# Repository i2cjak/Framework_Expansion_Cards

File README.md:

# i2cjak on X.com is THE foremost hardware engineer and poaster. he is designing one (1) new Framework Expansion Card per day until they give him a REALLY NICE laptop

# PROOF OF CHALLENGE!

## [Day 1](./Day_01_Wi-Fi-HaLow/)

Wi-Fi HaLow

## [Day 2](./Day_02_Four_Port_USB_C/)

Four Port USB-C

## [Day 3](./Day_03_ECG_SPO2/)

Electrocardiogram + SPO2

## [Day 4](./Day_04_Frameoscope/)

Frameoscope

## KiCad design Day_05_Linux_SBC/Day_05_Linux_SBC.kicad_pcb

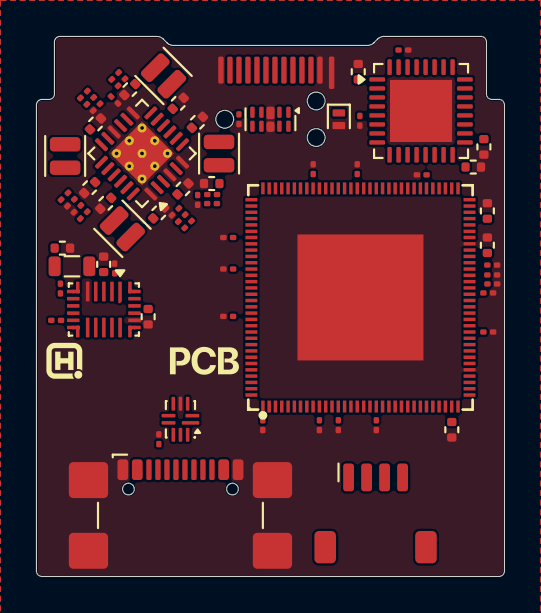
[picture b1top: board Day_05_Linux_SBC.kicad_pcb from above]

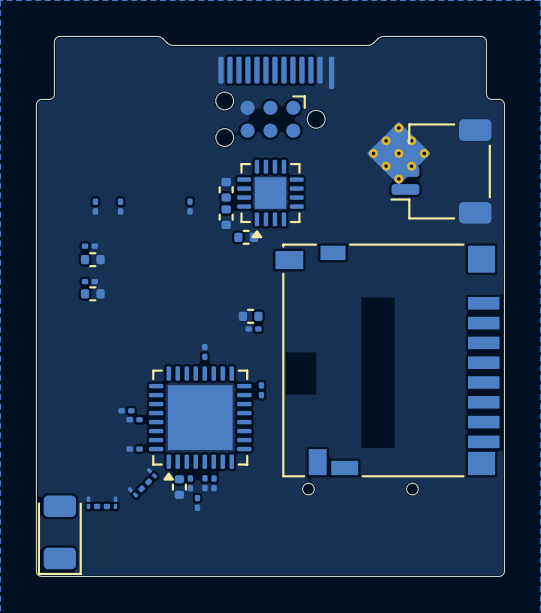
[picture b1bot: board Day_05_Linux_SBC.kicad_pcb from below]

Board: 8 copper layers, 26.0 x 30.0 mm, 108 parts (34 on the bottom side), 52 nets, no tracks yet.

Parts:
AE1: Antenna_Chip; Johanson_2450AT18x100_2400-2500Mhz
C1, C2, C4, C15, C16, C17, C18, C19, C23, C26, C38, C44, C45, C49, C55, C57, C64, C65, C66: 10uF; amemb-C_0402_1005Metric_L
C3, C21, C25, C27, C28, C29, C30, C31, C32, C33, C39, C40, C41, C42, C43, C46, C47, C48, C50, C51, C52, C53, C54, C56, C58, C59, C60, C61, C62, C63: 1uF; amemb-C_0201_0603Metric_L
C5, C6, C7, C10: 220pF; amemb-C_0201_0603Metric_L
C8: 47nF; amemb-C_0201_0603Metric_L
C9: 100nF; amemb-C_0201_0603Metric_L
C11, C12, C13, C14, C22: 22uF; amemb-C_0402_1005Metric_L
C20: 22nF; amemb-C_0201_0603Metric_L
C24: 4.7uF; amemb-C_0402_1005Metric_L
C34, C35, C36, C37: 1.2pF; amemb-C_01005_0402Metric_L
D1: TVS; D_SOD-882
H1, H2: MountingHole; MountingHole_2.2mm_M2
J1: USB_C_Plug_USB2.0; USB_C_Plug_Amphenol_12401981E412A
J2: Conn_ARM_SWD_TagConnect_TC2030-NL; Tag-Connect_TC2030-IDC-NL_2x03_P1.27mm_Vertical
J3: USB_C_Receptacle_USB2.0_14P; USB_C_Receptacle_GCT_USB4110
J4: JST SH SM03B; JST_SH_SM03B-SRSS-TB_1x03-1MP_P1.00mm_Horizontal
J5: Micro_SD_Card_Det2; microSD_HC_Hirose_DM3D-SF
L1, L2, L3, L4: 1.5uH; amemb-L_0806_2016Metric_L
L5: 1uH; amemb-L_0805_2012Metric_L
L6: 2.4nH; amemb-L_0201_0603Metric_L
L7: 0R; amemb-R_0201_0603Metric_L
LOGO1: NextPCB
R1: 5.1kR; amemb-R_0201_0603Metric_L
R2: 10kR; amemb-R_0201_0603Metric_L
R3, R13: 510kR; amemb-R_0201_0603Metric_L
R4, R5, R7, R9, R10, R12, R15, R16: 100kR; amemb-R_0201_0603Metric_L
R6: 80.6kR; amemb-R_0201_0603Metric_L
R8, R11: 200kR; amemb-R_0201_0603Metric_L
R14: 240R; amemb-R_0201_0603Metric_L
U1: D3V3XA4B10LP; Diodes_UDFN-10_1x2.5mm_P0.5mm
U2: STM32H503KBUx; QFN-32-1EP_5x5mm_P0.5mm_EP3.45x3.45mm
U3: CH334P; QFN-16-1EP_3x3mm_P0.5mm_EP1.75x1.75mm
U5: ESP32-C6FH4; QFN-32-1EP_5x5mm_P0.5mm_EP3.6x3.6mm
U6: RV1106G2; QFN-128_L12.3-W12.3-P0.35-TL-EP7.0-1
U7: STEMMA-QT; JST_SH_SM04B-SRSS-TB_1x04-1MP_P1.00mm_Horizontal
U8: EA3058QD; VQFN-24-1EP_4x4mm_P0.5mm_EP2.5x2.5mm_ThermalVias
U9: MP2722; QFN-22_MP2722_2.5x3.5mm_P0.4mm
U10: TS3USB30ERSWR; UQFN-10_1.4x1.8mm_P0.4mm

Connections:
+0V9: C7.1, C14.1, C38.1, C39.1, C40.1, C41.1, C46.1, C47.1, C48.1, C49.1, C50.1, C51.1, C52.1, L3.2, R7.1, U6.10 (VDD0V9), U6.51 (VDD0V9), U6.54 (VDD0V9), U6.55 (VDD0V9), U6.67 (VDD0V9), U6.71 (VDD0V9), U6.82 (VDD0V9), U6.103 (VDD0V9), U6.115 (VDD0V9), U6.116 (VDD0V9)
+1V8: C10.1, C12.1, C53.1, C54.1, C55.1, C58.1, L4.2, R11.1, U6.1 (GPIO7_VCC1V8), U6.24 (VDD1V8), U6.31 (VDD1V8), U6.53 (VDD1V8), U6.70 (VDD1V8), U6.96 (VDD1V8)
+1V35: C6.1, C13.1, C42.1, C43.1, C44.1, C45.1, L2.2, R5.1, U6.49 (DDR_VDDQ), U6.50 (DDR_VDDQ), U6.56 (DDR_VDDQ)
+3V3: C1.1, C2.1, C3.1, C5.1, C11.1, C25.1, C26.1, C27.1, C28.1, C29.1, C30.1, C31.1, C32.1, C33.1, C56.1, C57.1, C59.1, C60.1, C61.1, C62.1, C63.1, J2.1 (VCC), L1.2, R3.1, R16.1, U2.1 (VDD), U2.5 (VDDA), U2.17 (VDD), U5.2 (VDDA3P3), U5.3 (VDDA3P3), U5.5 (VDDPST1), U5.20 (VDDPST2), U5.29 (VDDA1), U5.32 (VDDA2), U6.13 (GPIO4_VCC), U6.19 (VDD3V3), U6.28 (VDD3V3), U6.43 (GPIO3_VCC), U6.61 (VDD3V3), U6.81 (VDD3V3), U6.88 (GPIO6_VCC), U6.101 (VDD3V3), U6.108 (GPIO5_VCC), U10.8 (~OE), U10.9 (VCC)
/D+: J1.A6 (D+), U1.4, U1.7 (NC), U3.12 (DPU+)
/D-: J1.A7 (D-), U1.2, U1.9 (NC), U3.11 (DMU-)
/ESP32-C6/ESP32.EN: R15.1, U5.4 (CHIP_PU)
/MPU_OUT.D+: J3.A6 (D+), J3.B6 (D+), U10.1 (D1+)
/MPU_OUT.D-: J3.A7 (D-), J3.B7 (D-), U10.7 (D1-)
/PMIC.CC1: J3.A5 (CC1), U9.1 (CC1)
/PMIC.CC2: J3.B5 (CC2), U9.22 (CC2)
/Power Supply/NTC: J4.2, R13.1, U9.10 (NTC1)
/Power Supply/VBUS_IO: C21.1, U9.2 (IN)
/RV1106G2/MPU.D+: U6.27 (USB_DP), U10.3 (D+)
/RV1106G2/MPU.D-: U6.26 (USB_DM), U10.5 (D-)
/STM32H5/SWCLK: J2.4 (SWCLK), U2.24 (DEBUG_JTCK-SWCLK)
/STM32H5/SWDIO: J2.2 (SWDIO), U2.23 (DEBUG_JTMS-SWDIO)
/STM32H5/~RESET: J2.3 (~RESET), U2.4 (NRST)
GND: C1.2, C2.2, C3.2, C4.2, C8.2, C9.2, C11.2, C12.2, C13.2, C14.2, C15.2, C16.2, C17.2, C18.2, C19.2, C21.2, C22.2, C23.2, C24.2, C25.2, C26.2, C27.2, C28.2, C29.2, C30.2, C31.2, C32.2, C33.2, C34.2, C35.2, C36.2, C37.2, C38.2, C39.2, C40.2, C41.2, C42.2, C43.2, C44.2, C45.2, C46.2, C47.2, C48.2, C49.2, C50.2, C51.2, C52.2, C53.2, C54.2, C55.2, C56.2, C57.2, C58.2, C59.2, C60.2, C61.2, C62.2, C63.2, C64.2, C65.2, C66.2, D1.2 (A), J1.A1 (GND), J1.A12 (GND), J1.B1 (GND), J1.B12 (GND), J1.SH (SHIELD), J2.5 (GND), J3.A1 (GND), J3.A12 (GND), J3.B1 (GND), J3.B12 (GND), J3.SH (SHIELD), J4.3, J4.MP (MountPin), R1.2, R2.2, R4.2, R6.2, R8.2, R12.2, R14.2, R15.2, U1.3 (VSS), U1.8 (VSS), U2.33 (VSS), U3.17 (GND), U5.33 (GND), U6.37 (VSS), U6.57 (VSS), U6.129 (VSS), U8.1 (GND), U8.4 (GND), U8.6 (GND), U8.13 (GND), U8.16 (GND), U8.25 (GND), U9.5 (GND), U9.18 (GND), U10.4 (GND)
unnamed: AE1.2 (PCB_Trace_2), C36.1, L7.1
unnamed: C35.1, C37.1, L6.1, L7.2
unnamed: D1.1 (K), J1.A4 (VBUS), J1.A9 (VBUS), J1.B4 (VBUS), J1.B9 (VBUS)
unnamed: J1.A5 (CC), R1.1
unnamed: J3.A4 (VBUS), J3.A9 (VBUS), J3.B4 (VBUS), J3.B9 (VBUS)
unnamed: J4.1, U9.12 (BATTSNS), U9.14 (BATT)
unnamed: R2.1, U2.31 (BOOT0)
unnamed: C4.1, U2.16 (VCAP)
unnamed: C64.1, U3.15 (V5)
unnamed: C65.1, C66.1, U3.16 (VDD33)
unnamed: C34.1, L6.2, U5.1 (ANT)
unnamed: R16.2, U5.15 (GPIO9)
unnamed: R14.1, U6.52 (RAM_ZQ)
unnamed: C9.1, R10.2, U8.10 (EN1)
unnamed: C8.1, R9.2, U8.9 (EN2), U8.22 (EN3)
unnamed: C5.2, R3.2, R4.1, U8.14 (FB1)
unnamed: C10.2, R11.2, R12.1, U8.5 (FB2)
unnamed: C6.2, R5.2, R6.1, U8.2 (FB3)
unnamed: C7.2, R7.2, R8.1, U8.15 (FB4)
unnamed: L1.1, U8.12 (LX1)
unnamed: L4.1, U8.7 (LX2)
unnamed: L2.1, U8.24 (LX3)
unnamed: L3.1, U8.19 (LX4)
unnamed: C19.1, U8.3 (VCC)
unnamed: C15.1, C16.1, C17.1, C18.1, C22.1, L5.2, U8.8 (VIN2), U8.11 (VIN1), U8.20 (VIN4), U8.23 (VIN3), U9.13 (SYS)
unnamed: C20.1, U9.6 (BST)
unnamed: C23.1, U9.3 (PMID)
unnamed: C20.2, L5.1, U9.4 (SW)
unnamed: C24.1, U9.19 (VCC)
unnamed: R13.2, U9.7 (VRNTC)
unnamed: U3.10 (DP1+), U10.2 (D2+)
unnamed: U3.9 (DM1-), U10.6 (D2-)
VIN: R9.1, R10.1, U8.21 (EN4)

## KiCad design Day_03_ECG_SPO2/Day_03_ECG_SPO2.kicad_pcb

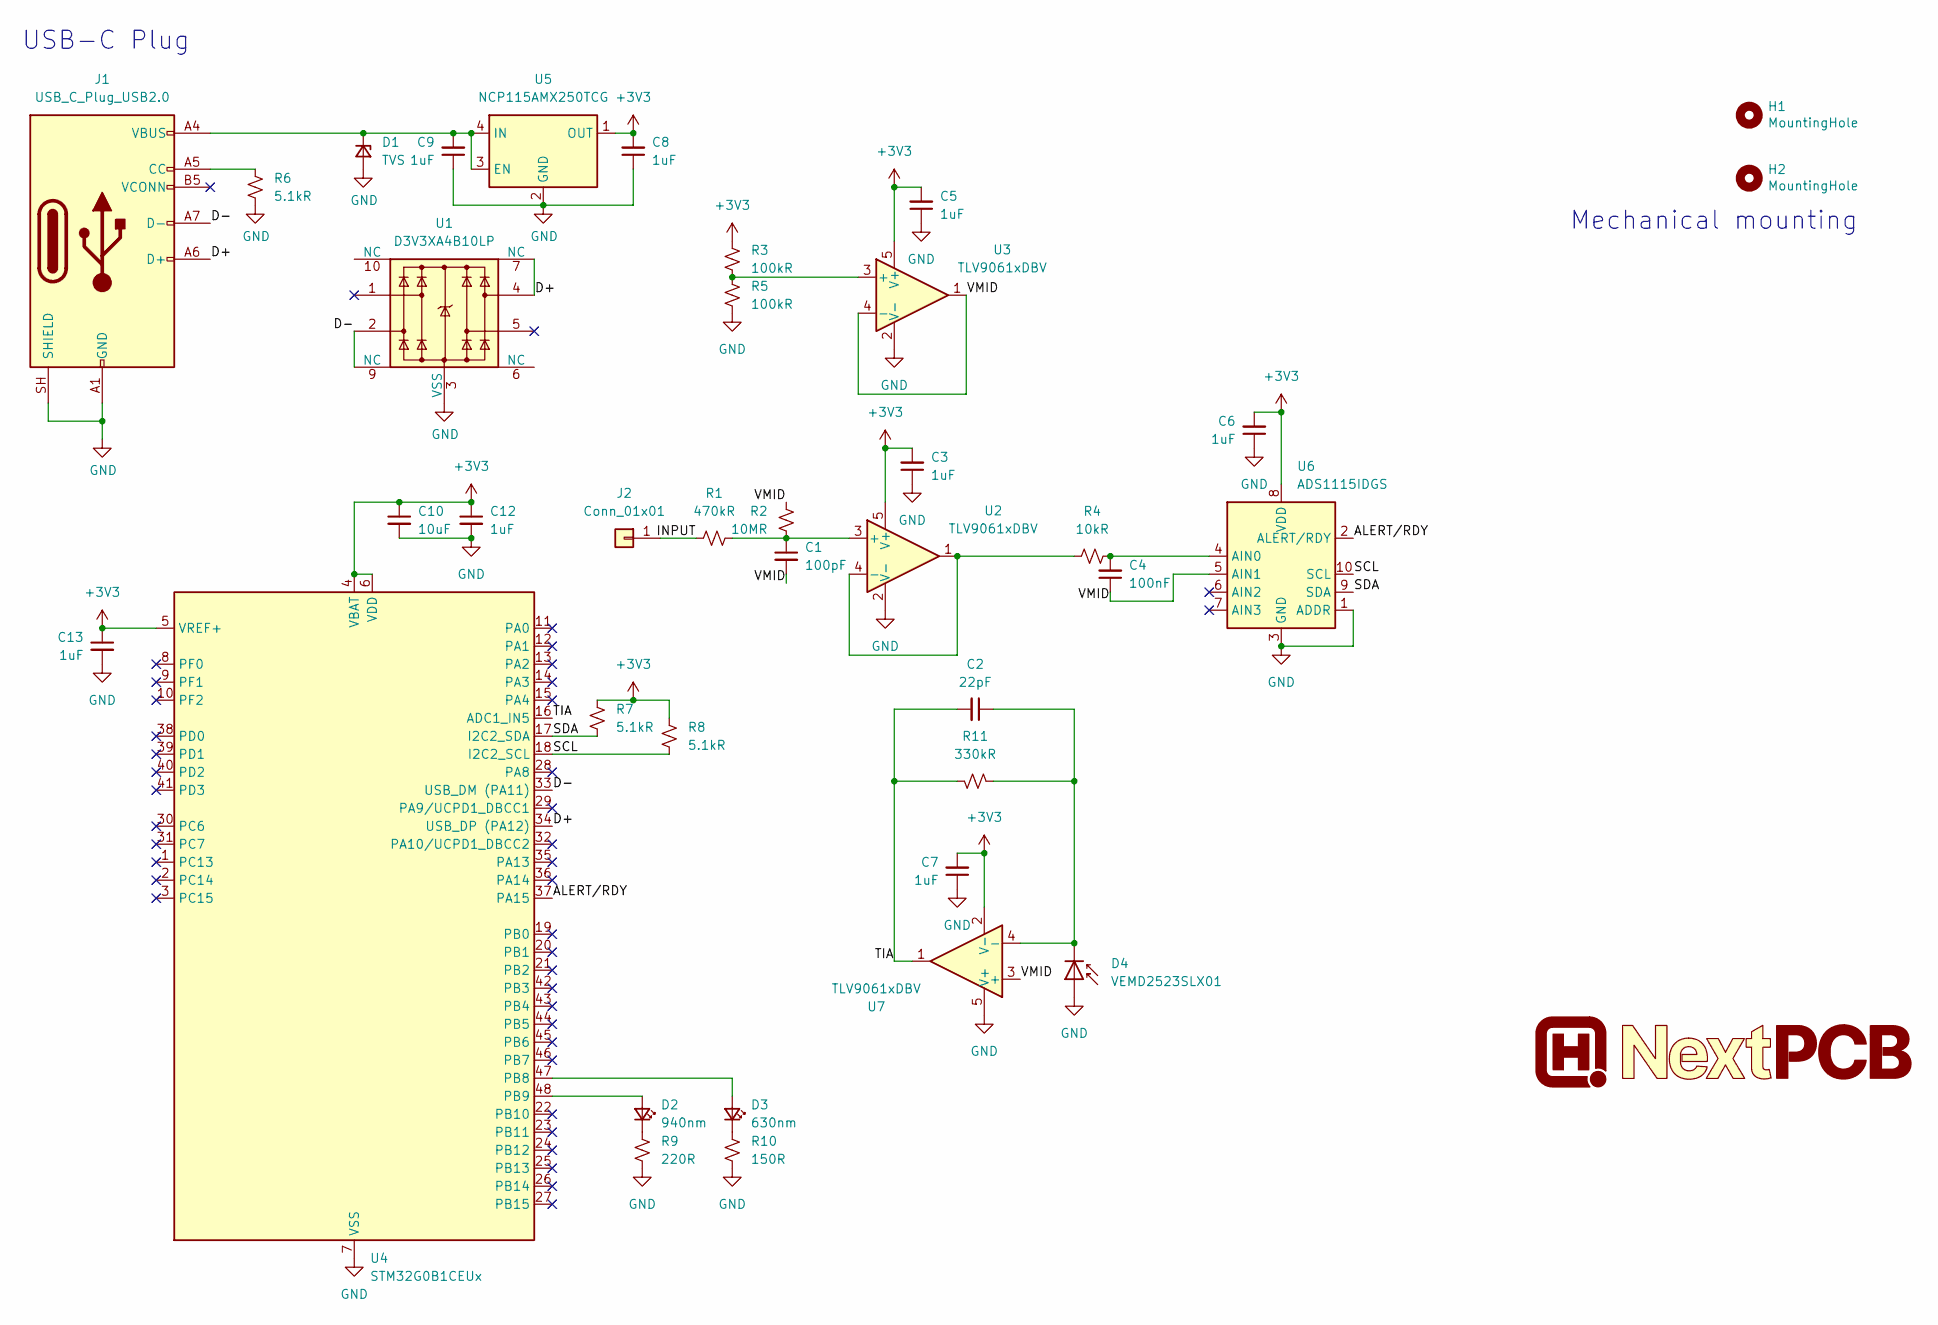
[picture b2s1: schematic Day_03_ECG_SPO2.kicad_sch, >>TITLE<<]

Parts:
C1: 100pF; C_0402_1005Metric
C2: 22pF; C_0402_1005Metric
C3, C5, C6, C7, C8, C9, C12, C13: 1uF; C_0402_1005Metric
C4: 100nF; C_0402_1005Metric
C10: 10uF; C_0402_1005Metric
D1: TVS; D_SOD-882
D2: 940nm; LED-SMD_3P-L3.0-W2.0_KPA-3010F3C
D3: 630nm; LED-SMD_L2.5-W1.2_KA-2810AVBS-D
D4: VEMD2523SLX01; OPTO-SMD_VEMD2523SLX01
H1, H2: MountingHole; MountingHole_2.2mm_M2
J1: USB_C_Plug_USB2.0; USB_C_Plug_Amphenol_12401981E412A
J2: Conn_01x01; ECG_Mount
LOGO1: NextPCB
R1: 470kR; R_0402_1005Metric
R2: 10MR; R_0402_1005Metric
R3, R5: 100kR; R_0402_1005Metric
R4: 10kR; R_0402_1005Metric
R6, R7, R8: 5.1kR; R_0402_1005Metric
R9: 220R; R_0402_1005Metric
R10: 150R; R_0402_1005Metric
R11: 330kR; R_0402_1005Metric
U1: D3V3XA4B10LP; Diodes_UDFN-10_1x2.5mm_P0.5mm
U2, U3, U7: TLV9061xDBV; SOT-23-5
U4: STM32G0B1CEUx; QFN-48-1EP_7x7mm_P0.5mm_EP5.6x5.6mm_ThermalVias
U5: NCP115AMX250TCG; OnSemi_XDFN4-1EP_1.0x1.0mm_EP0.52x0.52mm
U6: ADS1115IDGS; TSSOP-10_3x3mm_P0.5mm

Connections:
+3V3: C3.2, C5.2, C6.2, C7.2, C8.2, C10.1, C12.1, C13.1, R3.1, R7.1, R8.1, U2.5 (V+), U3.5 (V+), U4.4 (VBAT), U4.5 (VREF+), U4.6 (VDD), U5.1 (OUT), U6.8 (VDD), U7.2 (V-)
/ALERT/RDY: U4.37 (PA15), U6.2 (ALERT/RDY)
/D+: J1.A6 (D+), U1.4, U1.7 (NC), U4.34 (USB_DP (PA12))
/D-: J1.A7 (D-), U1.2, U1.9 (NC), U4.33 (USB_DM (PA11))
/INPUT: J2.1 (Pin_1_1), R1.1
/SCL: R8.2, U4.18 (I2C2_SCL), U6.10 (SCL)
/SDA: R7.2, U4.17 (I2C2_SDA), U6.9 (SDA)
/TIA: C2.2, R11.2, U4.16 (ADC1_IN5), U7.1
/VMID: C1.2, C4.1, R2.1, U3.1, U3.4 (-), U6.5 (AIN1), U7.3 (+)
GND: C3.1, C5.1, C6.1, C7.1, C8.1, C9.1, C10.2, C12.2, C13.2, D1.2 (A), D4.2 (A), J1.A1 (GND), J1.A12 (GND), J1.B1 (GND), J1.B12 (GND), J1.SH (SHIELD), R5.2, R6.2, R9.2, R10.2, U1.3 (VSS), U1.8 (VSS), U2.2 (V-), U3.2 (V-), U4.7 (VSS), U4.49 (VSS), U5.2 (GND), U5.5 (GND), U6.1 (ADDR), U6.3 (GND), U7.5 (V+)
unnamed: C9.2, D1.1 (K), J1.A4 (VBUS), J1.A9 (VBUS), J1.B4 (VBUS), J1.B9 (VBUS), U5.3 (EN), U5.4 (IN)
unnamed: D2.2 (A), U4.48 (PB9)
unnamed: D2.1 (K), R9.1
unnamed: D3.2 (A), U4.47 (PB8)
unnamed: D3.1 (K), R10.1
unnamed: C2.1, D4.1 (K), R11.1, U7.4 (-)
unnamed: J1.A5 (CC), R6.1
unnamed: C1.1, R1.2, R2.2, U2.3 (+)
unnamed: R4.1, U2.1, U2.4 (-)
unnamed: R3.2, R5.1, U3.3 (+)
unnamed: C4.2, R4.2, U6.4 (AIN0)

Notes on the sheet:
Mechanical mounting
USB-C Plug

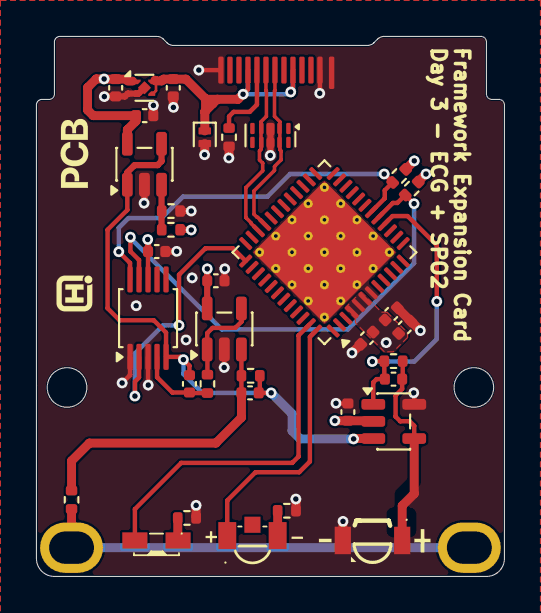
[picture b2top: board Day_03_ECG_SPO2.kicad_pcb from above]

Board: 4 copper layers, 26.0 x 30.0 mm, 39 parts (0 on the bottom side), 21 nets.

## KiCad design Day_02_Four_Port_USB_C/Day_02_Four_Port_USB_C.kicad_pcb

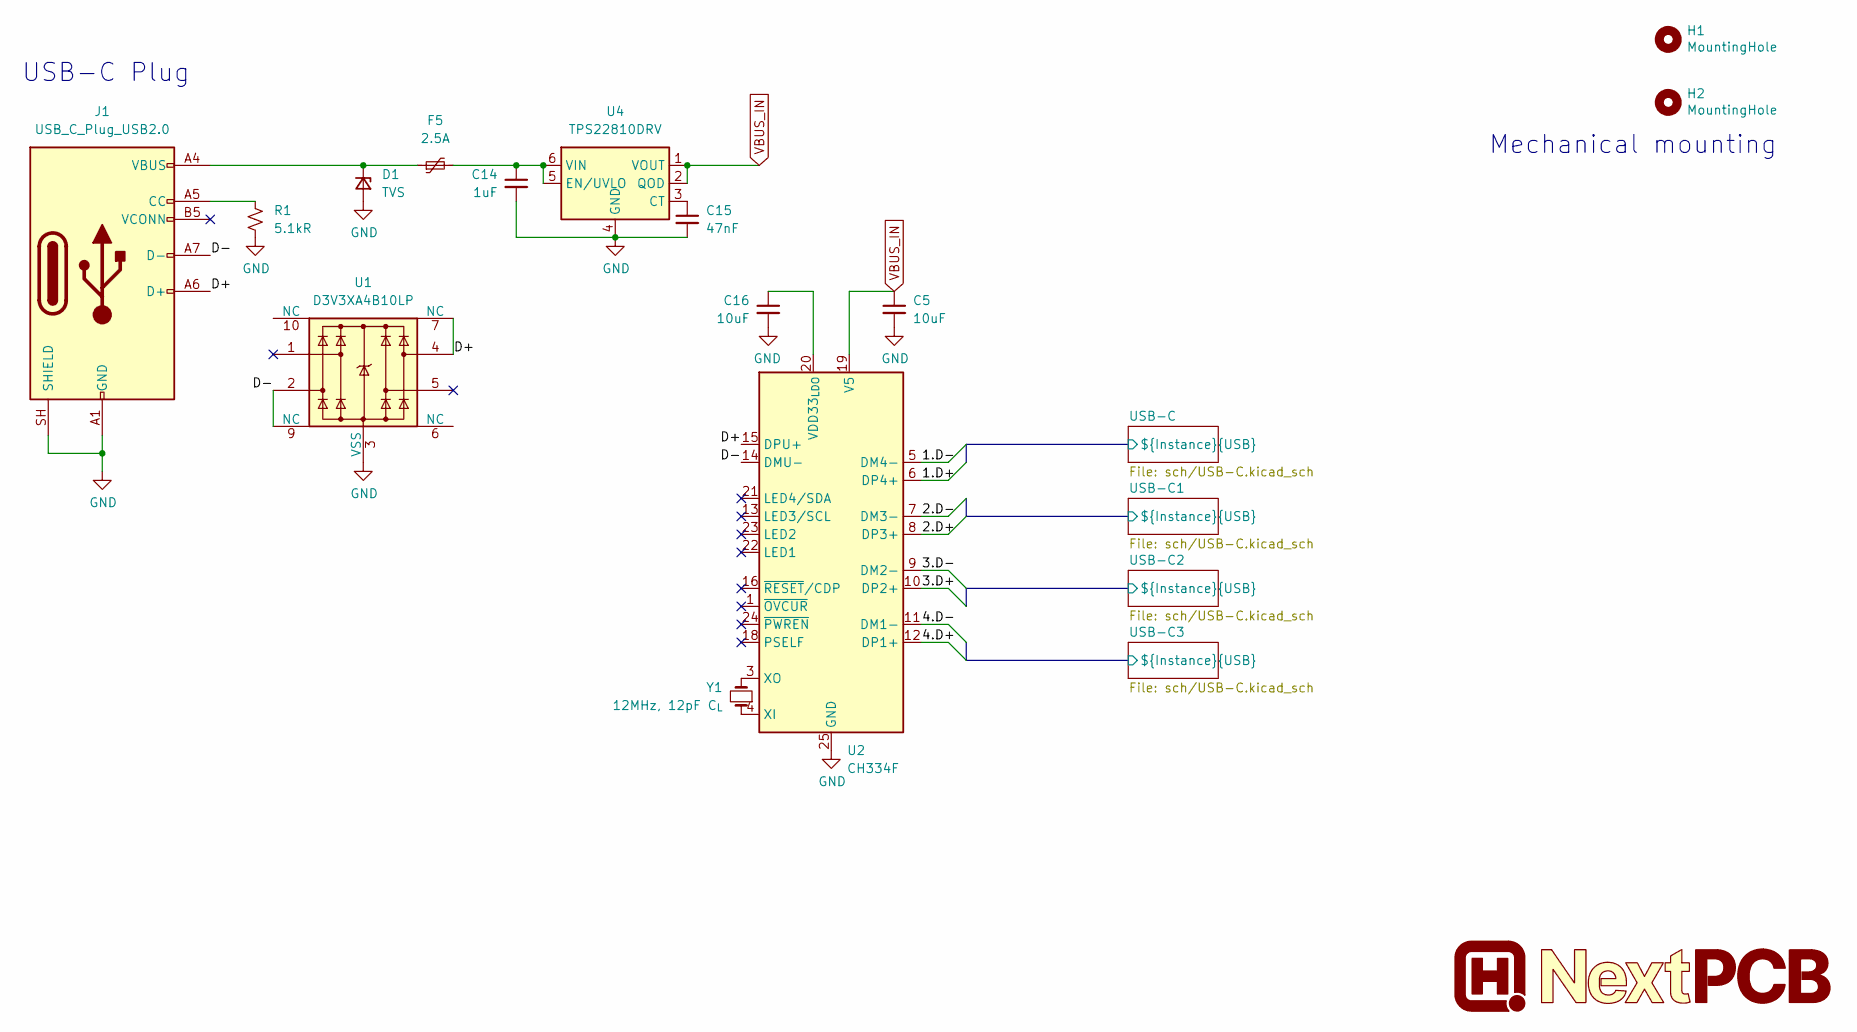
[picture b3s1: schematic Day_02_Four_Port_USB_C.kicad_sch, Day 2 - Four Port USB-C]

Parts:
C5, C16: 10uF; amemb-C_0402_1005Metric_L
C14: 1uF; amemb-C_0402_1005Metric_L
C15: 47nF; amemb-C_0402_1005Metric_L
D1: TVS; D_SOD-882
F5: 2.5A; Fuse_0805_2012Metric
H1, H2: MountingHole; MountingHole_2.2mm_M2
J1: USB_C_Plug_USB2.0; USB_C_Plug_Amphenol_12401981E412A
LOGO1: NextPCB
R1: 5.1kR; amemb-R_0402_1005Metric_L
U1: D3V3XA4B10LP; Diodes_UDFN-10_1x2.5mm_P0.5mm
U2: CH334F; QFN-24-1EP_4x4mm_P0.5mm_EP2.7x2.7mm_ThermalVias
U4: TPS22810DRV; WSON-6-1EP_2x2mm_P0.65mm_EP1x1.6mm
Y1: 12MHz, 12pF C_{L}

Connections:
/D+: J1.A6 (D+), U1.4, U1.7 (NC), U2.15 (DPU+)
/D-: J1.A7 (D-), U1.2, U1.9 (NC), U2.14 (DMU-)
/USB-C1/2.D+: U2.8 (DP3+); also elsewhere on the board
/USB-C1/2.D-: U2.7 (DM3-); also elsewhere on the board
/USB-C2/3.D+: U2.10 (DP2+); also elsewhere on the board
/USB-C2/3.D-: U2.9 (DM2-); also elsewhere on the board
/USB-C3/4.D+: U2.12 (DP1+); also elsewhere on the board
/USB-C3/4.D-: U2.11 (DM1-); also elsewhere on the board
/USB-C/1.D+: U2.6 (DP4+); also elsewhere on the board
/USB-C/1.D-: U2.5 (DM4-); also elsewhere on the board
GND: C5.2, C14.2, C15.2, C16.2, D1.2 (A), J1.A1 (GND), J1.A12 (GND), J1.B1 (GND), J1.B12 (GND), J1.SH (SHIELD), R1.2, U1.3 (VSS), U1.8 (VSS), U2.25 (GND), U4.4 (GND), U4.7 (GND); also elsewhere on the board
unnamed: D1.1 (K), F5.1, J1.A4 (VBUS), J1.A9 (VBUS), J1.B4 (VBUS), J1.B9 (VBUS)
unnamed: J1.A5 (CC), R1.1
unnamed: C16.1, U2.20 (VDD33_{LDO})
unnamed: U2.4 (XI), Y1.1
unnamed: U2.3 (XO), Y1.2
unnamed: C15.1, U4.3 (CT)
unnamed: C14.1, F5.2, U4.5 (EN/UVLO), U4.6 (VIN)
VBUS_IN: C5.1, U2.19 (V5), U4.1 (VOUT), U4.2 (QOD); also elsewhere on the board

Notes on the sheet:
Mechanical mounting
USB-C Plug

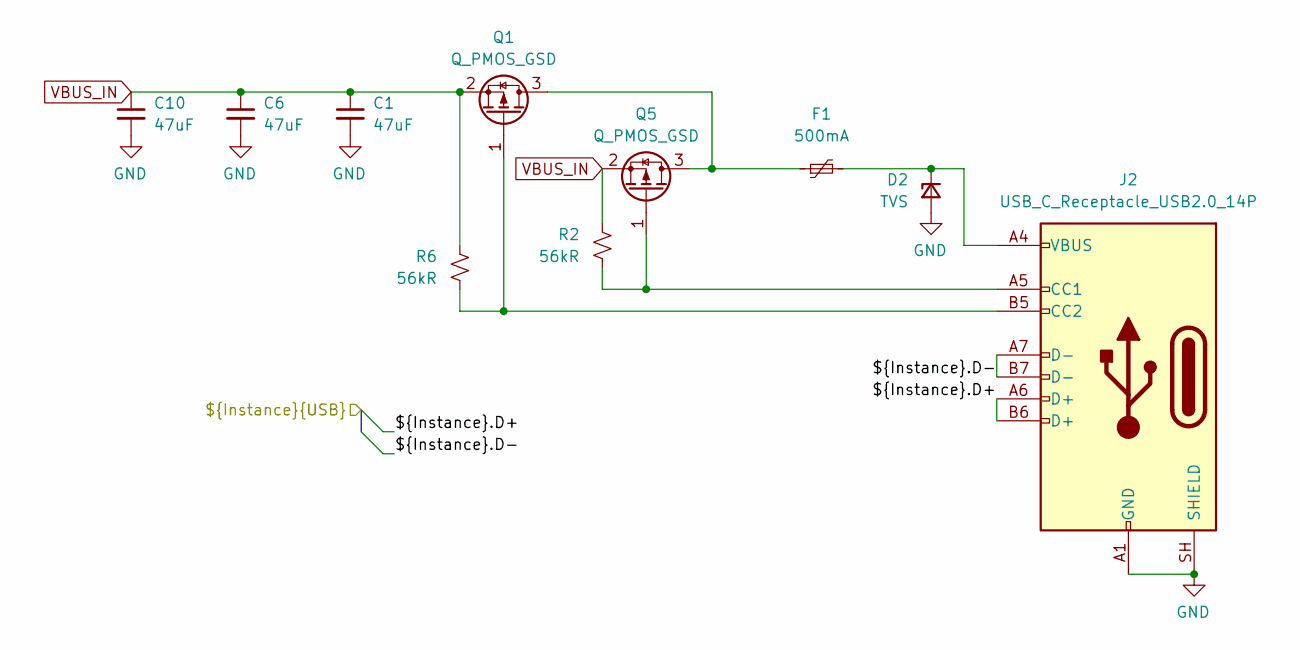
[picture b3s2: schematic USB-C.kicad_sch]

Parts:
C1, C6, C10: 47uF; amemb-C_0805_2012Metric_L
D2: TVS; D_SOD-882
F1: 500mA; Fuse_0402_1005Metric
J2: USB_C_Receptacle_USB2.0_14P; SAMESKY_UJ20-C-R-G-TH-P14
Q1, Q5: Q_PMOS_GSD; Diodes_DFN1006-3
R2, R6: 56kR; amemb-R_0402_1005Metric_L

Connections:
/USB-C/1.D+: J2.A6 (D+), J2.B6 (D+); also elsewhere on the board
/USB-C/1.D-: J2.A7 (D-), J2.B7 (D-); also elsewhere on the board
GND: C1.2, C6.2, C10.2, D2.2 (A), J2.A1 (GND), J2.A12 (GND), J2.B1 (GND), J2.B12 (GND), J2.SH (SHIELD); also elsewhere on the board
unnamed: D2.1 (K), F1.2, J2.A4 (VBUS), J2.A9 (VBUS), J2.B4 (VBUS), J2.B9 (VBUS)
unnamed: J2.A5 (CC1), Q5.1 (G), R2.2
unnamed: J2.B5 (CC2), Q1.1 (G), R6.2
unnamed: F1.1, Q1.3 (D), Q5.3 (D)
VBUS_IN: C1.1, C6.1, C10.1, Q1.2 (S), Q5.2 (S), R2.1, R6.1; also elsewhere on the board

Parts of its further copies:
C2, C3, C4, C7, C8, C9, C11, C12, C13: 47uF; amemb-C_0805_2012Metric_L
D3, D4, D5: TVS; D_SOD-882
F2, F3, F4: 500mA; Fuse_0402_1005Metric
J3, J4, J5: USB_C_Receptacle_USB2.0_14P; SAMESKY_UJ20-C-R-G-TH-P14
Q2, Q3, Q4, Q6, Q7, Q8: Q_PMOS_GSD; Diodes_DFN1006-3
R3, R4, R5, R7, R8, R9: 56kR; amemb-R_0402_1005Metric_L

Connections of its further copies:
/USB-C1/2.D+: J3.A6 (D+), J3.B6 (D+); also elsewhere on the board
/USB-C1/2.D-: J3.A7 (D-), J3.B7 (D-); also elsewhere on the board
/USB-C2/3.D+: J4.A6 (D+), J4.B6 (D+); also elsewhere on the board
/USB-C2/3.D-: J4.A7 (D-), J4.B7 (D-); also elsewhere on the board
/USB-C3/4.D+: J5.A6 (D+), J5.B6 (D+); also elsewhere on the board
/USB-C3/4.D-: J5.A7 (D-), J5.B7 (D-); also elsewhere on the board
GND: C2.2, C3.2, C4.2, C7.2, C8.2, C9.2, C11.2, C12.2, C13.2, D3.2 (A), D4.2 (A), D5.2 (A), J3.A1 (GND), J3.A12 (GND), J3.B1 (GND), J3.B12 (GND), J3.SH (SHIELD), J4.A1 (GND), J4.A12 (GND), J4.B1 (GND), J4.B12 (GND), J4.SH (SHIELD), J5.A1 (GND), J5.A12 (GND), J5.B1 (GND), J5.B12 (GND), J5.SH (SHIELD); also elsewhere on the board
unnamed: D3.1 (K), F2.2, J3.A4 (VBUS), J3.A9 (VBUS), J3.B4 (VBUS), J3.B9 (VBUS)
unnamed: D4.1 (K), F3.2, J4.A4 (VBUS), J4.A9 (VBUS), J4.B4 (VBUS), J4.B9 (VBUS)
unnamed: D5.1 (K), F4.2, J5.A4 (VBUS), J5.A9 (VBUS), J5.B4 (VBUS), J5.B9 (VBUS)
unnamed: J3.A5 (CC1), Q6.1 (G), R3.2
unnamed: J3.B5 (CC2), Q2.1 (G), R7.2
unnamed: J4.A5 (CC1), Q7.1 (G), R4.2
unnamed: J4.B5 (CC2), Q3.1 (G), R8.2
unnamed: J5.A5 (CC1), Q8.1 (G), R5.2
unnamed: J5.B5 (CC2), Q4.1 (G), R9.2
unnamed: F2.1, Q2.3 (D), Q6.3 (D)
unnamed: F3.1, Q3.3 (D), Q7.3 (D)
unnamed: F4.1, Q4.3 (D), Q8.3 (D)
VBUS_IN: C2.1, C3.1, C4.1, C7.1, C8.1, C9.1, C11.1, C12.1, C13.1, Q2.2 (S), Q3.2 (S), Q4.2 (S), Q6.2 (S), Q7.2 (S), Q8.2 (S), R3.1, R4.1, R5.1, R7.1, R8.1, R9.1; also elsewhere on the board

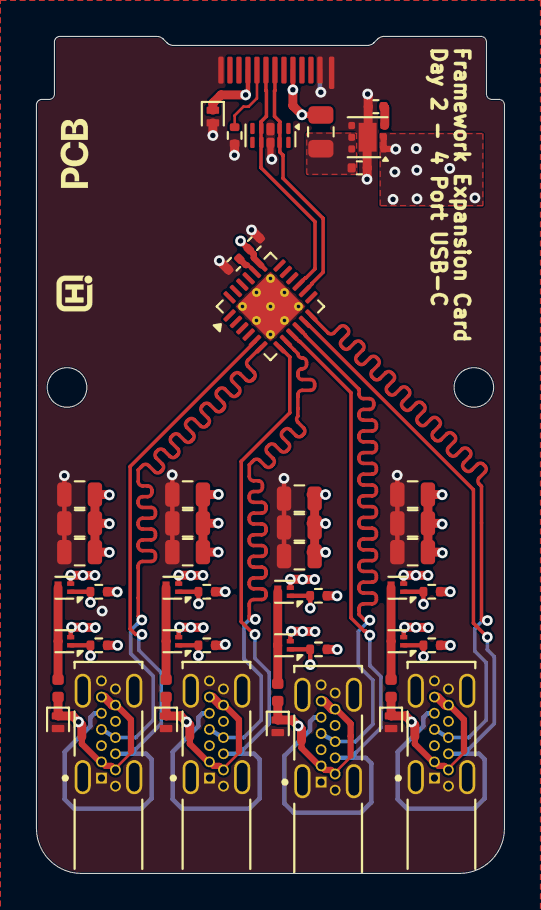
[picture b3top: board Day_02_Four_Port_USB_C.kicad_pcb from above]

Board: 4 copper layers, 26.0 x 46.5 mm, 54 parts (0 on the bottom side), 33 nets.

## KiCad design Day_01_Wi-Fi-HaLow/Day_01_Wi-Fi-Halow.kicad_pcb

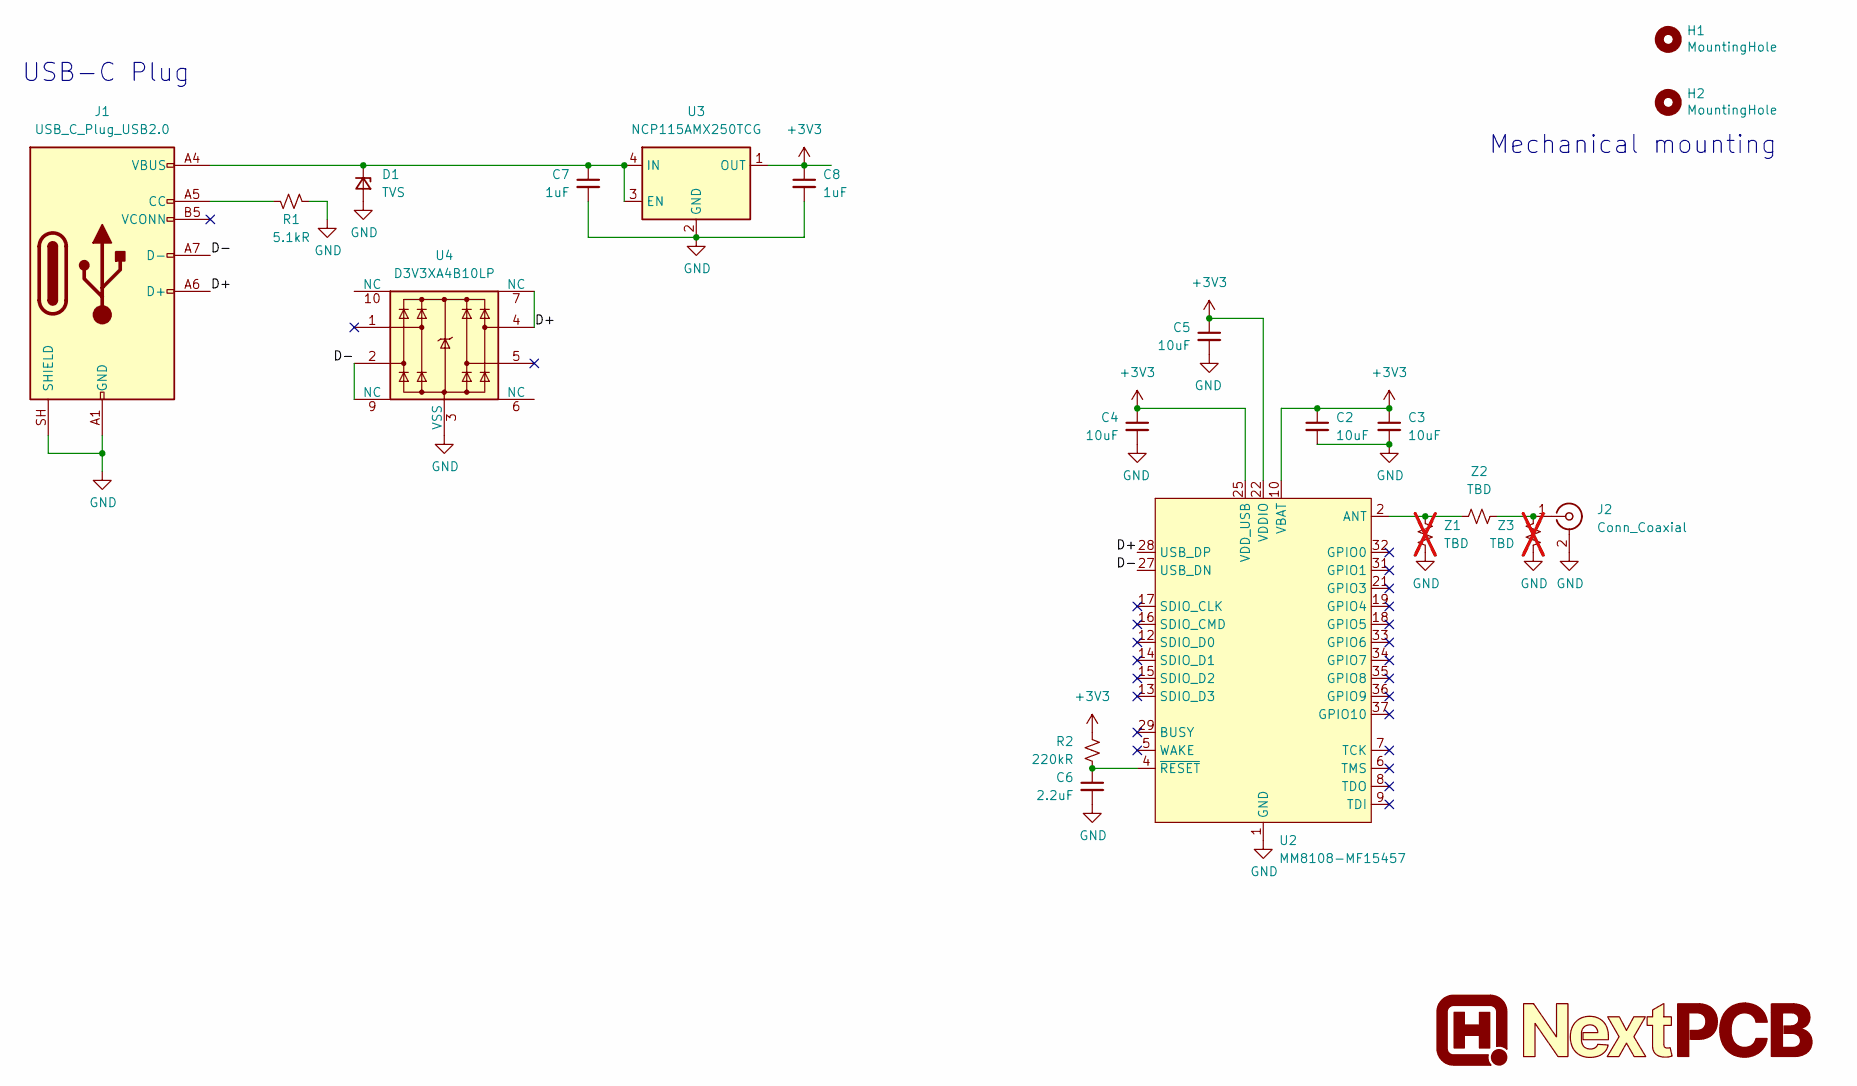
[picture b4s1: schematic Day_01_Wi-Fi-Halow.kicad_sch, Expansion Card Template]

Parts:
C2, C3, C4, C5: 10uF; amemb-C_0402_1005Metric_L
C6: 2.2uF; amemb-C_0402_1005Metric_L
C7, C8: 1uF; amemb-C_0402_1005Metric_L
D1: TVS; D_SOD-882
H1, H2: MountingHole; MountingHole_2.2mm_M2
J1: USB_C_Plug_USB2.0; USB_C_Plug_Amphenol_12401981E412A
J2: Conn_Coaxial; SMA_TE_CONSMA003.031-G_EdgeMount
LOGO1: NextPCB
R1: 5.1kR; amemb-R_0402_1005Metric_L
R2: 220kR; amemb-R_0402_1005Metric_L
U2: MM8108-MF15457; MorseMicro_MM8108-MF15457_LGA-38_11x10mm_P1mm_LayoutBorder1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
U3: NCP115AMX250TCG; OnSemi_XDFN4-1EP_1.0x1.0mm_EP0.52x0.52mm
U4: D3V3XA4B10LP; Diodes_UDFN-10_1x2.5mm_P0.5mm
Z1, Z3: TBD; amemb-R_0402_1005Metric_L; not fitted
Z2: TBD; amemb-R_0402_1005Metric_L

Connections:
+3V3: C2.1, C3.1, C4.1, C5.1, C8.1, R2.1, U2.10 (VBAT), U2.22 (VDDIO), U2.24 (VBAT_TX), U2.25 (VDD_USB), U3.1 (OUT)
/D+: J1.A6 (D+), U2.28 (USB_DP), U4.4, U4.7 (NC)
/D-: J1.A7 (D-), U2.27 (USB_DN), U4.2, U4.9 (NC)
GND: C2.2, C3.2, C4.2, C5.2, C6.2, C7.2, C8.2, D1.2 (A), J1.A1 (GND), J1.A12 (GND), J1.B1 (GND), J1.B12 (GND), J1.SH (SHIELD), J2.2 (Ext), R1.2, U2.1 (GND), U2.3 (GND), U2.11 (GND), U2.20 (GND), U2.23 (GND), U2.26 (GND), U2.30 (GND), U2.38 (GND), U3.2 (GND), U3.5 (GND), U4.3 (VSS), U4.8 (VSS), Z1.2, Z3.2
unnamed: C7.1, D1.1 (K), J1.A4 (VBUS), J1.A9 (VBUS), J1.B4 (VBUS), J1.B9 (VBUS), U3.3 (EN), U3.4 (IN)
unnamed: J1.A5 (CC), R1.1
unnamed: J2.1 (In), Z2.2, Z3.1
unnamed: U2.2 (ANT), Z1.1, Z2.1
unnamed: C6.1, R2.2, U2.4 (~RESET)

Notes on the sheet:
USB-C Plug
Mechanical mounting

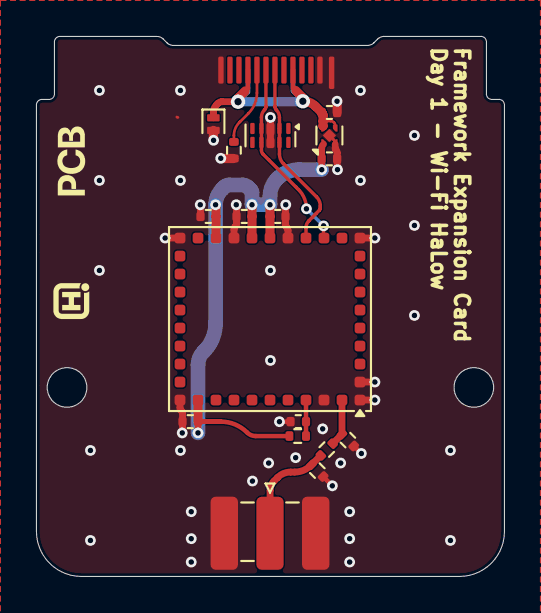
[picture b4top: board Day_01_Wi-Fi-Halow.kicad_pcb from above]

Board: 4 copper layers, 26.0 x 30.0 mm, 21 parts (0 on the bottom side), 9 nets.

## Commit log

2026-04-28 Initial commit.
2026-04-28 four port usb-c
2026-04-29 UPDATE WITH SPO2
2026-05-02 Update for Frameoscope
2026-05-02 Library updates
2026-05-02 Moved to Day 04
2026-05-06 Add USB isolator system spec

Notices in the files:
Day_01_Wi-Fi-HaLow/Day_01_Wi-Fi-Halow.kicad_pcb:
This work is licensed under a Creative Commons Attribution 4.0 International License
